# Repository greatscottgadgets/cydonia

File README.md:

# Cydonia

a 2.4 GHz receiver front-end based on [Quince](https://github.com/greatfet-hardware/quince)

## Project Status

Initial prototypes have not yet been assembled.

## Viewing or Modifying the Design

Required KiCad dependency:

https://github.com/greatscottgadgets/gsg-kicad-lib

If you are using git, the preferred way to install gsg-kicad-lib is to use the
submodule:

```
git submodule init && git submodule update
```

## Hardware Development Notes

See [Quince](https://github.com/greatfet-hardware/quince).

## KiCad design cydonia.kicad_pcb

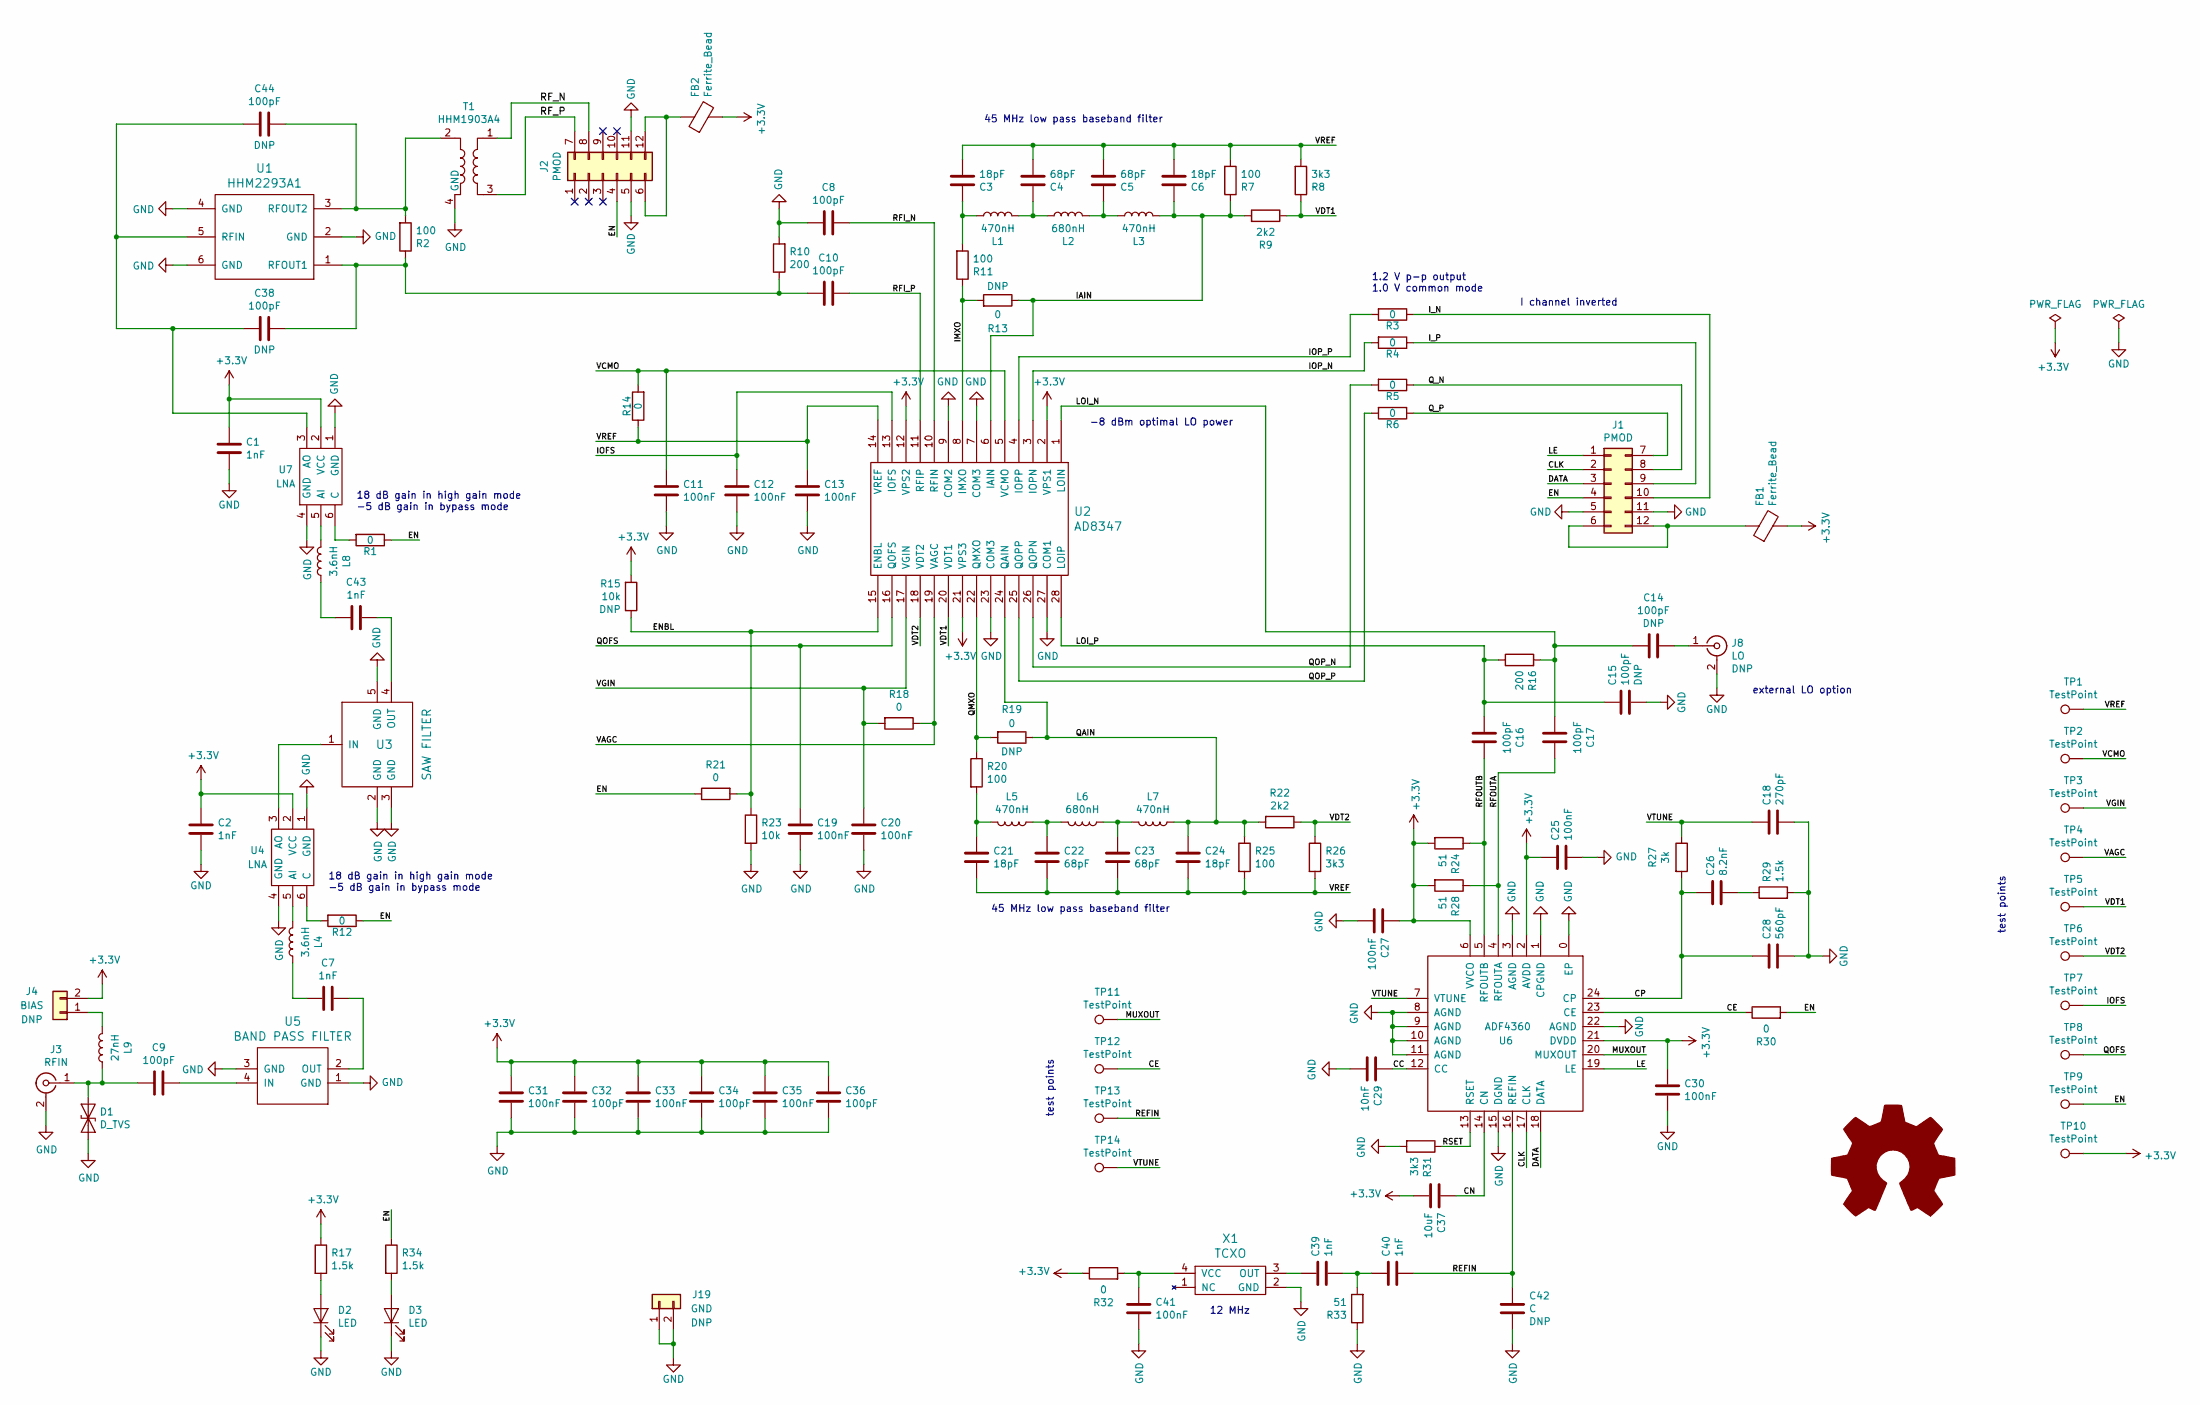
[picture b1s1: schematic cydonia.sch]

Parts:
C1, C2, C7, C39, C40, C43: 1nF; 0402; Part Number UMK105B7102KV-F
C3, C6, C21, C24: 18pF; 0402; Part Number CC0402JRNPO9BN180
C4, C5, C22, C23: 68pF; 0402; Part Number CL05C680JB5NNNC
C8, C9, C10, C14, C15, C16, C17, C32, C34, C36, C38, C44: 100pF; 0402; Part Number CL05C101JB5NNNC
C11, C12, C13, C19, C20, C25, C27, C30, C31, C33, C35, C41: 100nF; 0402; Part Number ‎CL05A104KP5NNNC‎
C18: 270pF; 0402; Part Number CC0402KRX7R9BB271
C26: 8.2nF; 0402; Part Number CC0402KRX7R7BB822
C28: 560pF; 0402; Part Number CC0402KRX7R8BB561
C29: 10nF; 0402; Part Number CL05B103KB5NNNC
C37: 10uF; 0805; Part Number CL21A106KPFNNNG
C42: C; 0402
D1: D_TVS; 0402; Part Number ESDSLC5V0L2B-TP
D2, D3: LED; 0603D
FB1, FB2: Ferrite_Bead; 0805; Part Number BLM21PG221SN1D
J1, J2: PMOD; PinHeader_2x06_P2.54mm_PMOD; Part Number PPPC062LJBN-RC
J3: RFIN; SMA-EDGE; Part Number CONREVSMA003.062
J4: BIAS; HEADER-1x2
J8: LO; SMA-VERTICAL; Part Number 5-1814832-1
J19: GND; HEADER-1x2
L1, L3, L5, L7: 470nH; 0402; Part Number LK1005R47K-TV
L2, L6: 680nH; 0402; Part Number LK1005R68K-TV
L4, L8: 3.6nH; 0402; Part Number HK10053N6S-T
L9: 27nH; 0402; Part Number HK100527NJ-T
R1, R3, R4, R5, R6, R12, R13, R14, R18, R19, R21, R30, R32: 0; 0402; Part Number RC0402JR-070RL
R2, R7, R11, R20, R25: 100; 0402; Part Number RC0402JR-07100RL
R8, R26, R31: 3k3; 0402; Part Number RC0402JR-073K3L
R9, R22: 2k2; 0402; Part Number RC0402JR-072K2L
R10, R16: 200; 0402; Part Number RC0402JR-07200RL
R15, R23: 10k; 0402; Part Number RC0402JR-0710KL
R17, R29, R34: 1.5k; 0402; Part Number RC0402JR-071K5L
R24, R28, R33: 51; 0402; Part Number RC0402JR-0751RL
R27: 3k; 0402; Part Number RC0402JR-073KL
T1: HHM1903A4; Part Number HHM1903A4
TP1, TP2, TP3, TP4, TP5, TP6, TP7, TP8, TP9, TP10, TP11, TP12, TP13, TP14: TestPoint; TESTPOINT-50MIL
U1: HHM2293A1; Part Number HHM2293A1
U2: AD8347; TSSOP28; Part Number AD8347ARUZ-REEL7
U3: SAW FILTER; B9413; Part Number B39242B9413K610
U4, U7: LNA; BGA7H1N6; Part Number BGA5H1BN6E6327XTSA1
U5: BAND PASS FILTER; 2450BP39D100C; Part Number 2450BP39D100CE
U6: ADF4360; QFN24-4; Part Number ADF4360-0BCPZ
X1: TCXO; XTAL5.0x3.2mm; Part Number FT5HNBPK12.0-T1

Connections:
+3V3: C1.2, C2.2, C25.1, C27.1, C30.1, C31.1, C32.2, C33.1, C34.2, C35.1, C36.2, C37.2, FB1.2, FB2.2, J4.2, R15.2, R17.1, R24.2, R28.2, R32.1, TP10.1, U2.2 (VPS1), U2.12 (VPS2), U2.21 (VPS3), U4.2 (VCC), U6.2 (AVDD), U6.6 (VVCO), U6.21 (DVDD), U7.2 (VCC)
/CC: C29.1, U6.12 (CC)
/CE: R30.1, TP12.1, U6.23 (CE)
/CLK: J1.2, U6.17 (CLK)
/CN: C37.1, U6.14 (CN)
/CP: C26.2, C28.2, R27.2, U6.24 (CP)
/DATA: J1.3, U6.18 (DATA)
/EN: J1.4, J2.4, R1.1, R12.1, R21.1, R30.2, R34.1, TP9.1
/ENBL: R15.1, R21.2, R23.1, U2.15 (ENBL)
/IAIN: C6.1, L3.1, R7.1, R9.2, R13.1, U2.6 (IAIN)
/IMXO: R11.1, R13.2, U2.8 (IMXO)
/IOFS: C12.1, TP7.1, U2.13 (IOFS)
/IOP_N: R4.2, U2.3 (IOPN)
/IOP_P: R3.2, U2.4 (IOPP)
/I_N: J1.10, R3.1
/I_P: J1.9, R4.1
/LE: J1.1, U6.19 (LE)
/LOI_N: C14.2, C17.2, R16.2, U2.1 (LOIN)
/LOI_P: C15.2, C16.2, R16.1, U2.28 (LOIP)
/MUXOUT: TP11.1, U6.20 (MUXOUT)
/QAIN: C24.1, L7.1, R19.1, R22.2, R25.1, U2.24 (QAIN)
/QMXO: R19.2, R20.1, U2.22 (QMXO)
/QOFS: C19.1, TP8.1, U2.16 (QOFS)
/QOP_N: R5.2, U2.26 (QOPN)
/QOP_P: R6.2, U2.25 (QOPP)
/Q_N: J1.8, R5.1
/Q_P: J1.7, R6.1
/REFIN: C40.2, C42.2, TP13.1, U6.16 (REFIN)
/RFI_N: C8.1, U2.10 (RFIN)
/RFI_P: C10.1, U2.11 (RFIP)
/RFOUTA: C17.1, R28.1, U6.4 (RFOUTA)
/RFOUTB: C16.1, R24.1, U6.5 (RFOUTB)
/RF_N: J2.8, T1.1
/RF_P: J2.7, T1.3
/RSET: R31.1, U6.13 (RSET)
/VAGC: R18.1, TP4.1, U2.19 (VAGC)
/VCMO: C11.1, R14.2, TP2.1, U2.5 (VCMO)
/VDT1: R8.1, R9.1, TP5.1, U2.20 (VDT1)
/VDT2: R22.1, R26.1, TP6.1, U2.18 (VDT2)
/VGIN: C20.1, R18.2, TP3.1, U2.17 (VGIN)
/VREF: C3.2, C4.2, C5.2, C6.2, C13.1, C21.2, C22.2, C23.2, C24.2, R7.2, R8.2, R14.1, R25.2, R26.2, TP1.1, U2.14 (VREF)
/VTUNE: C18.2, R27.1, TP14.1, U6.7 (VTUNE)
GND: C1.1, C2.1, C8.2, C11.2, C12.2, C13.2, C15.1, C18.1, C19.2, C20.2, C25.2, C27.2, C28.1, C29.2, C30.2, C31.2, C32.1, C33.2, C34.1, C35.2, C36.1, C41.2, C42.1, D1.2 (A2), D2.1 (K), D3.1 (K), J1.5, J1.11, J2.5, J2.11, J3.2 (Ext), J8.2 (Ext), J19.1, J19.2, R10.2, R23.2, R29.2, R31.2, R33.1, T1.4 (GND), U1.2 (GND), U1.4 (GND), U1.6 (GND), U2.7 (COM3), U2.9 (COM2), U2.23 (COM3), U2.27 (COM1), U3.2 (GND), U3.3 (GND), U3.5 (GND), U4.1 (GND), U4.4 (GND), U5.1 (GND), U5.3 (GND), U6.0 (EP), U6.1 (CPGND), U6.3 (AGND), U6.8 (AGND), U6.9 (AGND), U6.10 (AGND), U6.11 (AGND), U6.15 (DGND), U6.22 (AGND), U7.1 (GND), U7.4 (GND), X1.2 (GND)
unnamed: C3.1, L1.2, R11.2
unnamed: C4.1, L1.1, L2.2
unnamed: C5.1, L2.1, L3.2
unnamed: C7.1, L4.2
unnamed: C7.2, U5.2 (OUT)
unnamed: C9.1, U5.4 (IN)
unnamed: C9.2, D1.1 (A1), J3.1 (In), L9.2
unnamed: C10.2, C38.1, R2.1, R10.1, U1.1 (RFOUT1)
unnamed: C14.1, J8.1 (In)
unnamed: C21.1, L5.2, R20.2
unnamed: C22.1, L5.1, L6.2
unnamed: C23.1, L6.1, L7.2
unnamed: C26.1, R29.1
unnamed: C38.2, C44.2, U1.5 (RFIN), U7.3 (AO)
unnamed: C39.1, X1.3 (OUT)
unnamed: C39.2, C40.1, R33.2
unnamed: C41.1, R32.2, X1.4 (VCC)
unnamed: C43.1, L8.2
unnamed: C43.2, U3.4 (OUT)
unnamed: C44.1, R2.2, T1.2, U1.3 (RFOUT2)
unnamed: D2.2 (A), R17.2
unnamed: D3.2 (A), R34.2
unnamed: FB1.1, J1.6, J1.12
unnamed: FB2.1, J2.6, J2.12
unnamed: J4.1, L9.1
unnamed: L4.1, U4.5 (AI)
unnamed: L8.1, U7.5 (AI)
unnamed: R1.2, U7.6 (C)
unnamed: R12.2, U4.6 (C)
unnamed: U3.1 (IN), U4.3 (AO)

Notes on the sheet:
45 MHz low pass baseband filter
1.2 V p-p output 1.0 V common mode
external LO option
-8 dBm optimal LO power
test points
12 MHz
I channel inverted
18 dB gain in high gain mode -5 dB gain in bypass mode

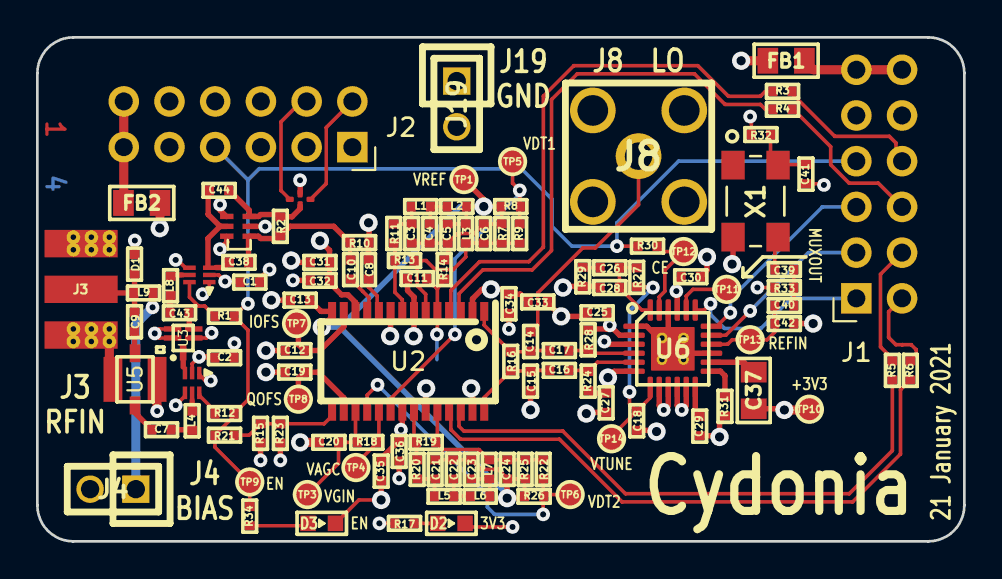
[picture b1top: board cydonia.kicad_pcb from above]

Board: 4 copper layers, 51.5 x 28.0 mm, 121 parts (1 on the bottom side), 73 nets.

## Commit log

2021-01-24 cydonia: initial commit, based on quince

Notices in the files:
cydonia.kicad_pcb:
Copyright © 2019-2021 Great Scott Gadgets
Licensed under the CERN-OHL-P v2
cydonia.sch:
License: CERN-OHL-P v2
